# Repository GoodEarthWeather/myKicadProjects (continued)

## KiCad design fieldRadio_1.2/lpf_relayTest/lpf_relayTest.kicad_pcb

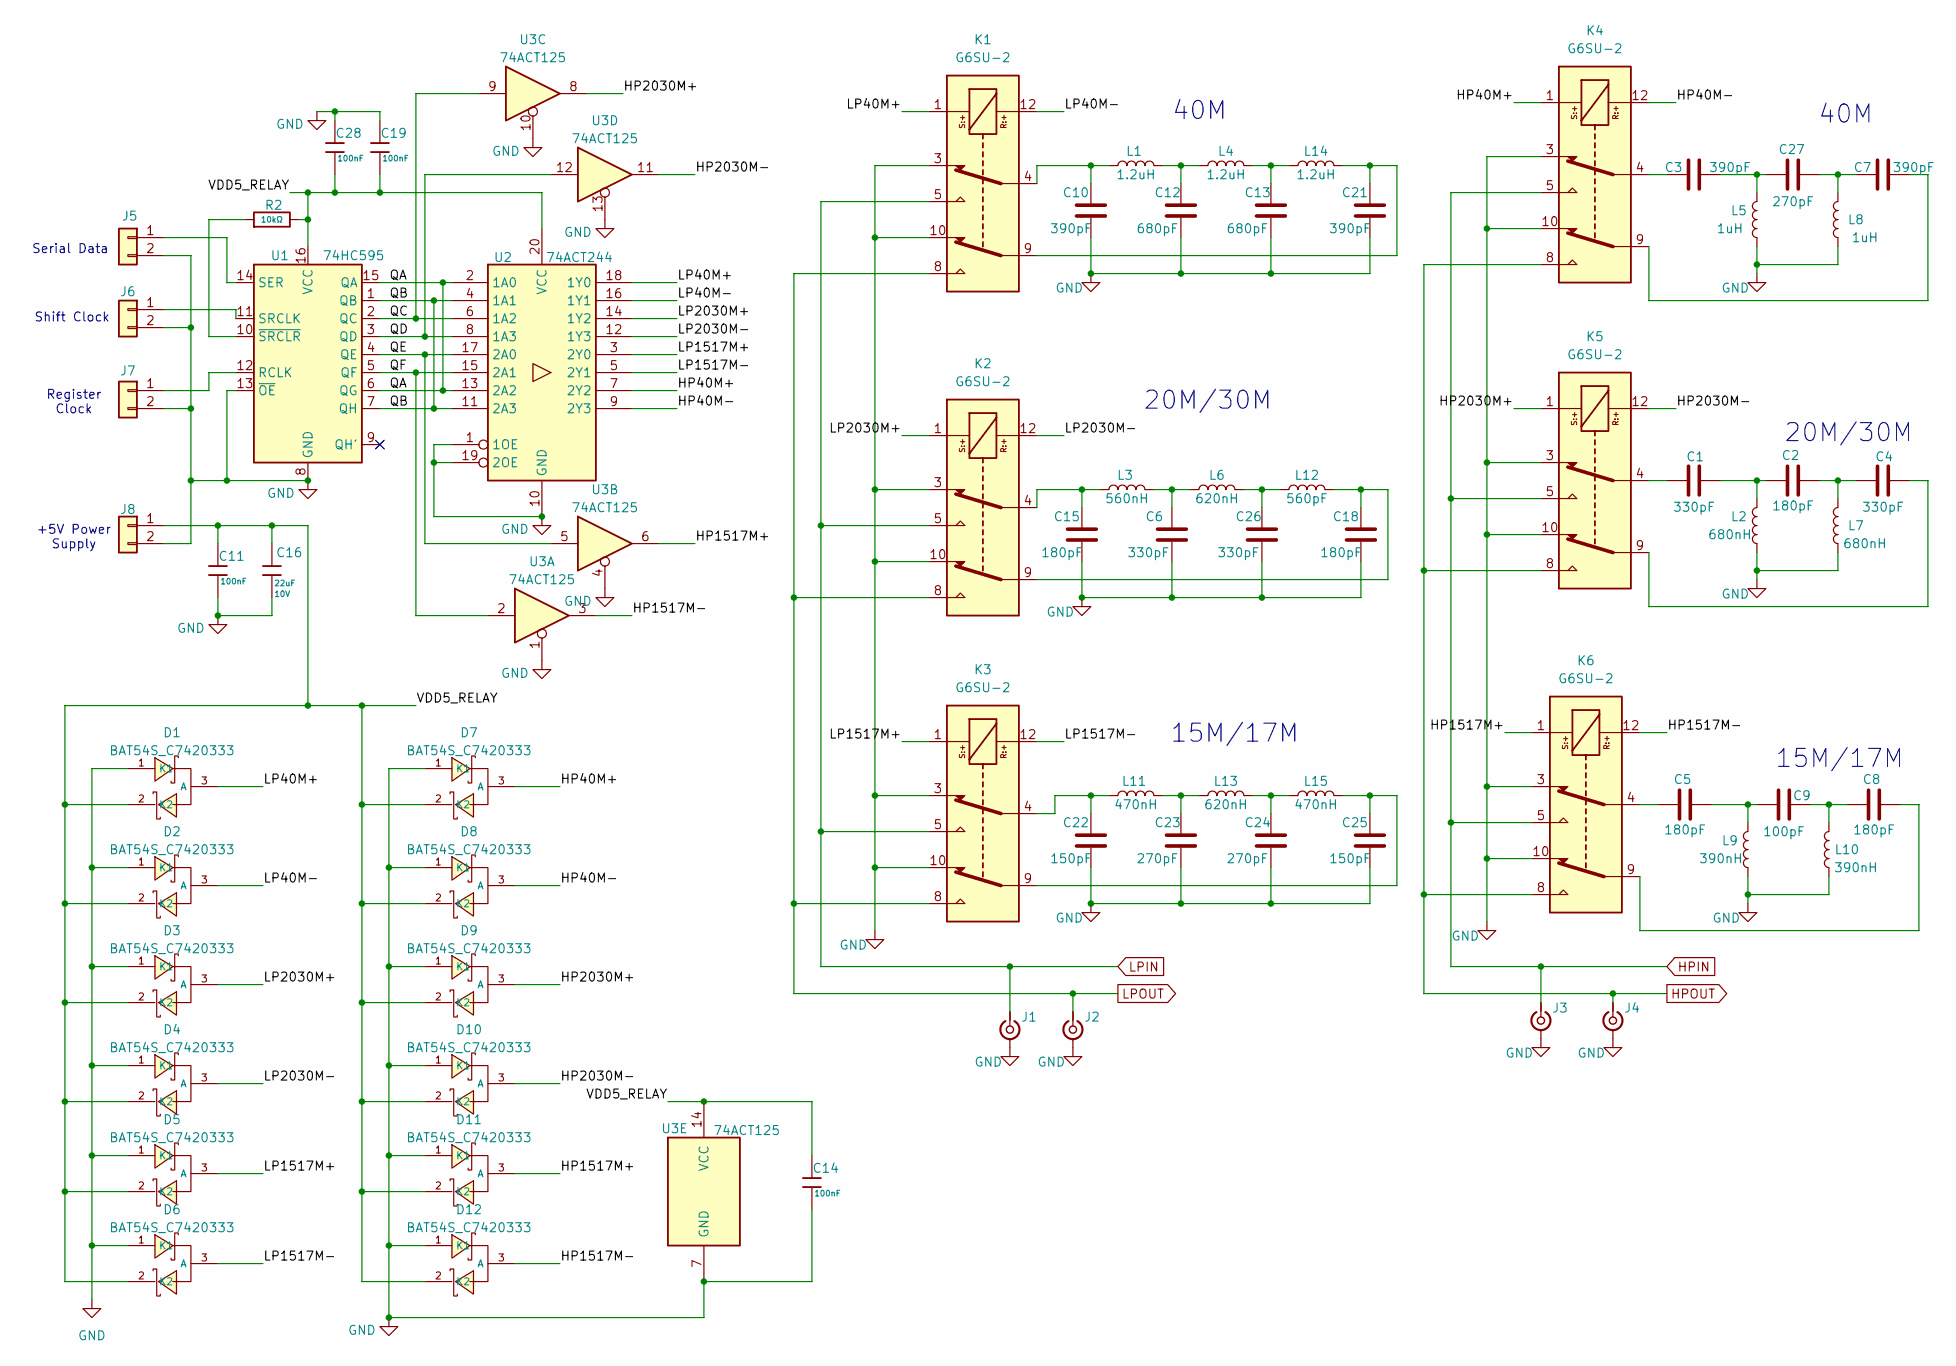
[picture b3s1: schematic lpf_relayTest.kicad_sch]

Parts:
C1, C4, C6, C26: 330pF; C_0805_2012Metric_Pad1.18x1.45mm_HandSolder; jlcpcb C113820
C2, C5, C8, C15, C18: 180pF; C_0805_2012Metric_Pad1.18x1.45mm_HandSolder; jlcpcb C527205
C3, C7, C10, C21: 390pF; C_0805_2012Metric_Pad1.18x1.45mm_HandSolder; jlcpcb C527206
C9: 100pF; C_0805_2012Metric_Pad1.18x1.45mm_HandSolder; jlcpcb C107105
C11, C14, C19, C28: 100nF; C_0603; Voltage Rated 50V; Tolerance ±10%; Part CC0603KRX7R9BB104; LCSC C14663
C12, C13: 680pF; C_0805_2012Metric_Pad1.18x1.45mm_HandSolder; jlcpcb C513601
C16: 22uF; C_1206; Voltage Rated 10V; Tolerance ±10%; Part CL31A226KPHNNNE; LCSC C5672
C22, C25: 150pF; C_0805_2012Metric_Pad1.18x1.45mm_HandSolder; jlcpcb C576916
C23, C24, C27: 270pF; C_0805_2012Metric_Pad1.18x1.45mm_HandSolder; jlcpcb C107106
D1, D2, D3, D4, D5, D6, D7, D8, D9, D10, D11, D12: BAT54S_C7420333; SOT-23-3_L2.9-W1.3-P1.90-LS2.4-BR; Reverse Voltage (Vr) 30V; Forward Voltage (Vf@If) 0.4V@10mA; Part BAT54S; LCSC C7420333
J1, J2, J3, J4: Conn_Coaxial_Small; SMA_Samtec_SMA-J-P-H-ST-EM1_EdgeMount
J5, J6, J7, J8: Conn_01x02; PinHeader_1x02_P2.54mm_Vertical
K1, K2, K3, K4, K5, K6: G6SU-2; Relay_DPDT_Omron_G6S-2F; Mouser Part Number 653-G6SU-2F-TRDC5
L1, L4, L14: 1.2uH; L_Toroid_Vertical_L13.0mm_W6.5mm_P5.60mm
L2, L7: 680nH; L_Toroid_Vertical_L13.0mm_W6.5mm_P5.60mm
L3: 560nH; L_Toroid_Vertical_L13.0mm_W6.5mm_P5.60mm
L5, L8: 1uH; L_Toroid_Vertical_L13.0mm_W6.5mm_P5.60mm
L6, L13: 620nH; L_Toroid_Vertical_L13.0mm_W6.5mm_P5.60mm
L9, L10: 390nH; L_Toroid_Vertical_L13.0mm_W6.5mm_P5.60mm
L11, L15: 470nH; L_Toroid_Vertical_L13.0mm_W6.5mm_P5.60mm
L12: 560pF; L_Toroid_Vertical_L13.0mm_W6.5mm_P5.60mm
R2: 10kΩ; R_0603; Overload Voltage (Max) 75V; Tolerance ±1%; Part 0603WAF1002T5E; LCSC C25804
U1: 74HC595; SOIC-16_3.9x9.9mm_P1.27mm; jlcpcb C10092
U2: 74ACT244; TSSOP-20_4.4x6.5mm_P0.65mm; jlcpcb C6930
U3: 74ACT125; SOIC-14_3.9x8.7mm_P1.27mm; jlcpcb C113254

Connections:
/HP40M+: D7.3 (A), K4.1, U2.7 (2Y2)
/HP40M-: D8.3 (A), K4.12, U2.9 (2Y3)
/HP1517M+: D11.3 (A), K6.1, U3.6
/HP1517M-: D12.3 (A), K6.12, U3.3
/HP2030M+: D9.3 (A), K5.1, U3.8
/HP2030M-: D10.3 (A), K5.12, U3.11
/LP40M+: D1.3 (A), K1.1, U2.18 (1Y0)
/LP40M-: D2.3 (A), K1.12, U2.16 (1Y1)
/LP1517M+: D5.3 (A), K3.1, U2.3 (2Y0)
/LP1517M-: D6.3 (A), K3.12, U2.5 (2Y1)
/LP2030M+: D3.3 (A), K2.1, U2.14 (1Y2)
/LP2030M-: D4.3 (A), K2.12, U2.12 (1Y3)
/QA: U1.6 (QG), U1.15 (QA), U2.2 (1A0), U2.13 (2A2)
/QB: U1.1 (QB), U1.7 (QH), U2.4 (1A1), U2.11 (2A3)
/QC: U1.2 (QC), U2.6 (1A2), U3.9
/QD: U1.3 (QD), U2.8 (1A3), U3.12
/QE: U1.4 (QE), U2.17 (2A0), U3.5
/QF: U1.5 (QF), U2.15 (2A1), U3.2
/VDD5_RELAY: C11.1, C14.1, C16.1, C19.2, C28.2, D1.2 (K2), D2.2 (K2), D3.2 (K2), D4.2 (K2), D5.2 (K2), D6.2 (K2), D7.2 (K2), D8.2 (K2), D9.2 (K2), D10.2 (K2), D11.2 (K2), D12.2 (K2), J8.1, R2.2, U1.16 (VCC), U2.20 (VCC), U3.14 (VCC)
GND: C6.2, C10.2, C11.2, C12.2, C13.2, C14.2, C15.2, C16.2, C18.2, C19.1, C21.2, C22.2, C23.2, C24.2, C25.2, C26.2, C28.1, D1.1 (K1), D2.1 (K1), D3.1 (K1), D4.1 (K1), D5.1 (K1), D6.1 (K1), D7.1 (K1), D8.1 (K1), D9.1 (K1), D10.1 (K1), D11.1 (K1), D12.1 (K1), J1.2 (Ext), J2.2 (Ext), J3.2 (Ext), J4.2 (Ext), J5.2, J6.2, J7.2, J8.2, K1.3, K1.10, K2.3, K2.10, K3.3, K3.10, K4.3, K4.10, K5.3, K5.10, K6.3, K6.10, L2.2, L5.2, L7.2, L8.2, L9.2, L10.2, U1.8 (GND), U1.13 (~OE), U2.1 (1OE), U2.10 (GND), U2.19 (2OE), U3.1, U3.4, U3.7 (GND), U3.10, U3.13
HPIN: J3.1 (In), K4.5, K5.5, K6.5
HPOUT: J4.1 (In), K4.8, K5.8, K6.8
LPIN: J1.1 (In), K1.5, K2.5, K3.5
LPOUT: J2.1 (In), K1.8, K2.8, K3.8
unnamed: C1.1, K5.4
unnamed: C1.2, C2.1, L2.1
unnamed: C2.2, C4.1, L7.1
unnamed: C3.1, K4.4
unnamed: C4.2, K5.9
unnamed: C5.1, K6.4
unnamed: C5.2, C9.2, L9.1
unnamed: C6.1, L3.2, L6.1
unnamed: C7.2, K4.9
unnamed: C8.1, C9.1, L10.1
unnamed: C8.2, K6.9
unnamed: C10.1, K1.4, L1.1
unnamed: C12.1, L1.2, L4.1
unnamed: C13.1, L4.2, L14.1
unnamed: C15.1, K2.4, L3.1
unnamed: C18.1, K2.9, L12.2
unnamed: C21.1, K1.9, L14.2
unnamed: C22.1, K3.4, L11.1
unnamed: C23.1, L11.2, L13.1
unnamed: C24.1, L13.2, L15.1
unnamed: C25.1, K3.9, L15.2
unnamed: C26.1, L6.2, L12.1
unnamed: C3.2, C27.1, L5.1
unnamed: C7.1, C27.2, L8.1
unnamed: J5.1, U1.14 (SER)
unnamed: J6.1, U1.11 (SRCLK)
unnamed: J7.1, U1.12 (RCLK)
unnamed: R2.1, U1.10 (~SRCLR)

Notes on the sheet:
15M/17M
Serial Data
Register Clock
Shift Clock
20M/30M
40M
+5V Power Supply

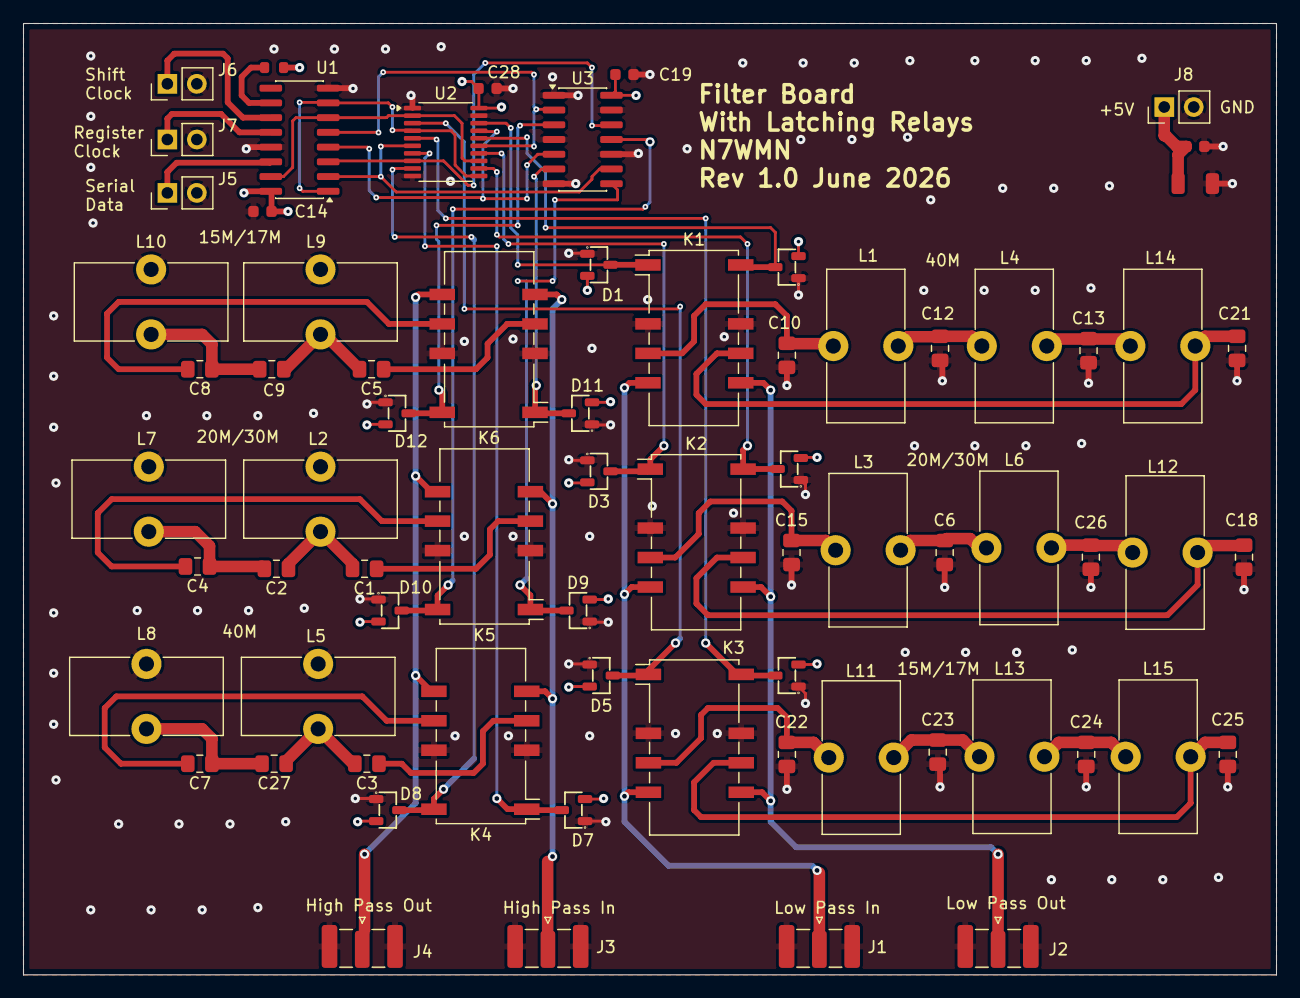
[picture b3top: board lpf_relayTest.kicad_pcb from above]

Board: 4 copper layers, 108.0 x 82.0 mm, 71 parts (0 on the bottom side), 52 nets.

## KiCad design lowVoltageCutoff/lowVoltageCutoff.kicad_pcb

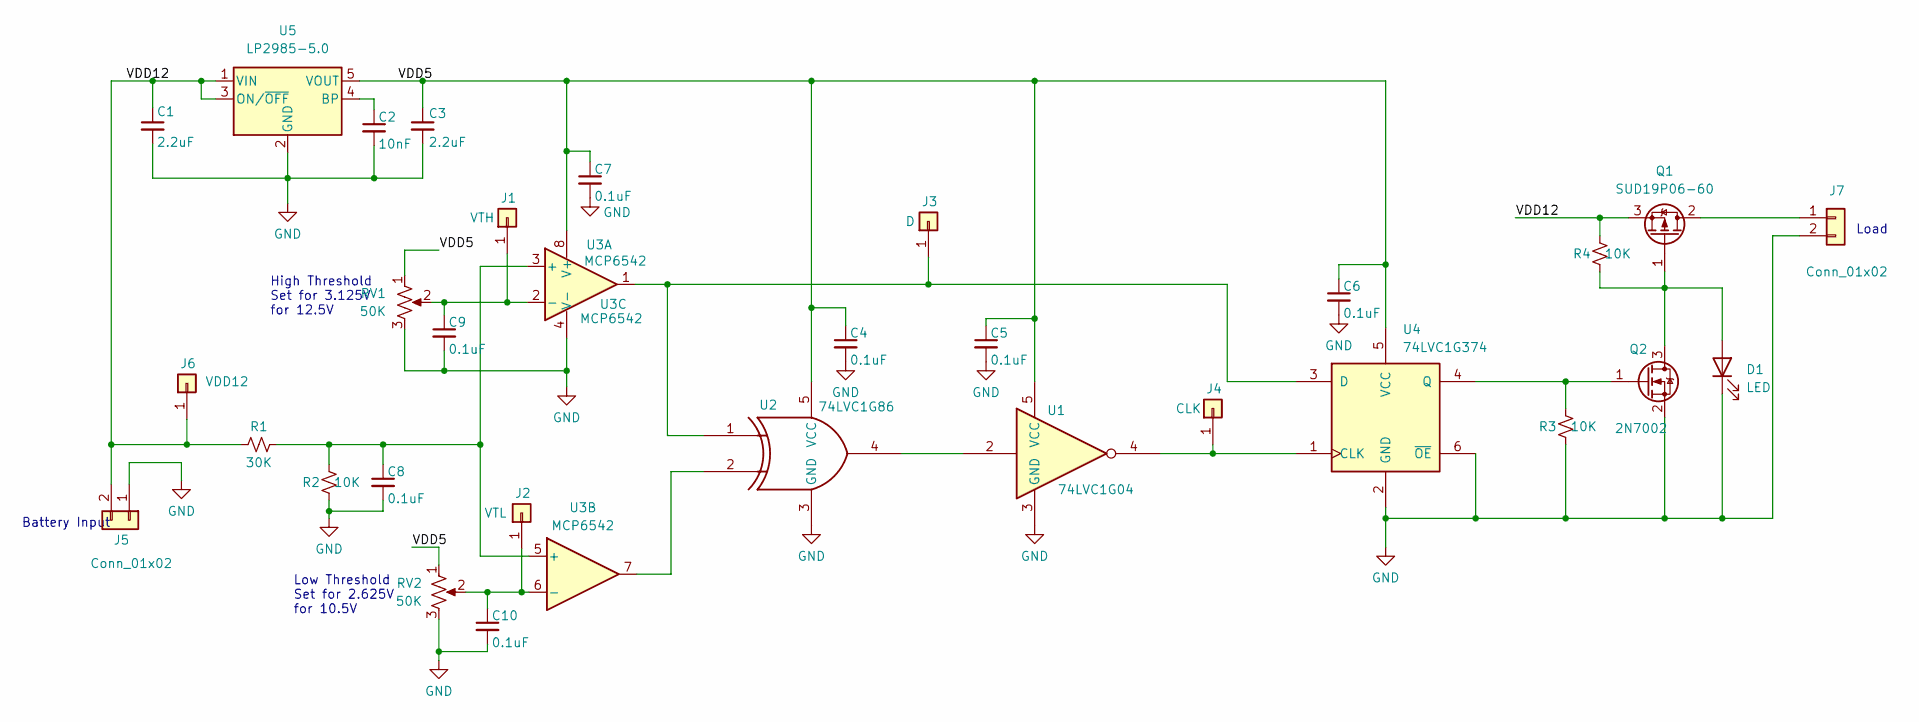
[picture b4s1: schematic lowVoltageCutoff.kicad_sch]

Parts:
C1, C3: 2.2uF; C_0603_1608Metric_Pad1.08x0.95mm_HandSolder
C2: 10nF; C_0603_1608Metric_Pad1.08x0.95mm_HandSolder
C4, C5, C6, C7, C8, C9, C10: 0.1uF; C_0603_1608Metric_Pad1.08x0.95mm_HandSolder
D1: LED; LED_D5.0mm
J1: VTH; PinHeader_1x01_P2.54mm_Vertical
J2: VTL; PinHeader_1x01_P2.54mm_Vertical
J3: D; PinHeader_1x01_P2.54mm_Vertical
J4: CLK; PinHeader_1x01_P2.54mm_Vertical
J5, J7: Conn_01x02; PinHeader_1x02_P2.54mm_Vertical
J6: VDD12; PinHeader_1x01_P2.54mm_Vertical
Q1: SUD19P06-60; TO-252-2; Mouser PN 781-SUD19P06-60L-E3
Q2: 2N7002; SOT-23
R1: 30K; R_0603_1608Metric_Pad0.98x0.95mm_HandSolder
R2, R3, R4: 10K; R_0603_1608Metric_Pad0.98x0.95mm_HandSolder
RV1, RV2: 50K; Potentiometer_Bourns_3296W_Vertical
U1: 74LVC1G04; SOT-23-5_HandSoldering; MouserPN 595-SN74LVC1G04DBVR
U2: 74LVC1G86; SOT-23-5_HandSoldering; Mouser PN 595-SN74LVC1G86DBVR
U3: MCP6542; SOIC-8_3.9x4.9mm_P1.27mm; Mouser PN 579-MCP6542T-I/SN
U4: 74LVC1G374; SOT-23-6_Handsoldering; Mouser PN 595-SN74LVC1G374DBVR
U5: LP2985-5.0; SOT-23-5_HandSoldering; Mouser PN 926-LP2985AIM5X50NPB

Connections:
/VDD5: C3.1, C4.1, C5.1, C6.1, C7.1, RV1.1, RV2.1, U1.5 (VCC), U2.5 (VCC), U3.8 (V+), U4.5 (VCC), U5.5 (VOUT)
/VDD12: C1.1, J5.2, J6.1, Q1.3 (S), R1.1, R4.2, U5.1 (VIN), U5.3 (ON/~OFF)
GND: C1.2, C2.2, C3.2, C4.2, C5.2, C6.2, C7.2, C8.2, C9.2, C10.2, D1.1 (K), J5.1, J7.2, Q2.2 (S), R2.1, R3.1, RV1.3, RV2.3, U1.3 (GND), U2.3 (GND), U3.4 (V-), U4.2 (GND), U4.6 (~OE), U5.2 (GND)
unnamed: D1.2 (A), Q1.1 (G), Q2.3 (D), R4.1
unnamed: C9.1, J1.1, RV1.2, U3.2 (-)
unnamed: C10.1, J2.1, RV2.2, U3.6 (-)
unnamed: J3.1, U2.1, U3.1, U4.3 (D)
unnamed: J4.1, U1.4, U4.1 (CLK)
unnamed: J7.1, Q1.2 (D)
unnamed: Q2.1 (G), R3.2, U4.4 (Q)
unnamed: U1.2, U2.4
unnamed: U2.2, U3.7
unnamed: C8.1, R1.2, R2.2, U3.3 (+), U3.5 (+)
unnamed: C2.1, U5.4 (BP)

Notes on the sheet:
Load
Battery Input
Low Threshold Set for 2.625V for 10.5V
High Threshold Set for 3.125V for 12.5V

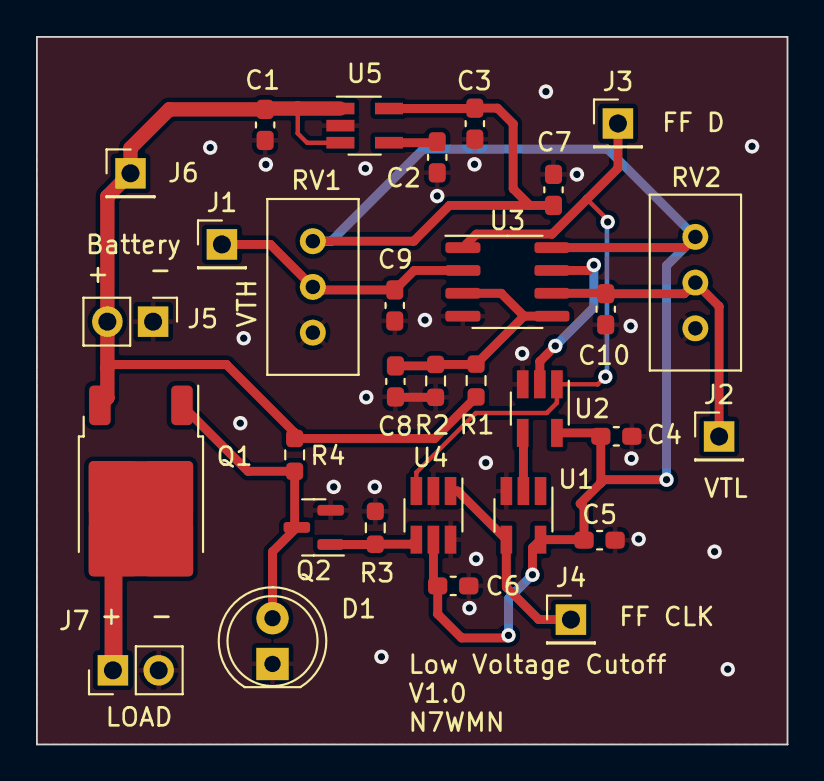
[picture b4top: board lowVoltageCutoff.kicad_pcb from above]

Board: 2 copper layers, 41.7 x 39.3 mm, 31 parts (0 on the bottom side), 14 nets.

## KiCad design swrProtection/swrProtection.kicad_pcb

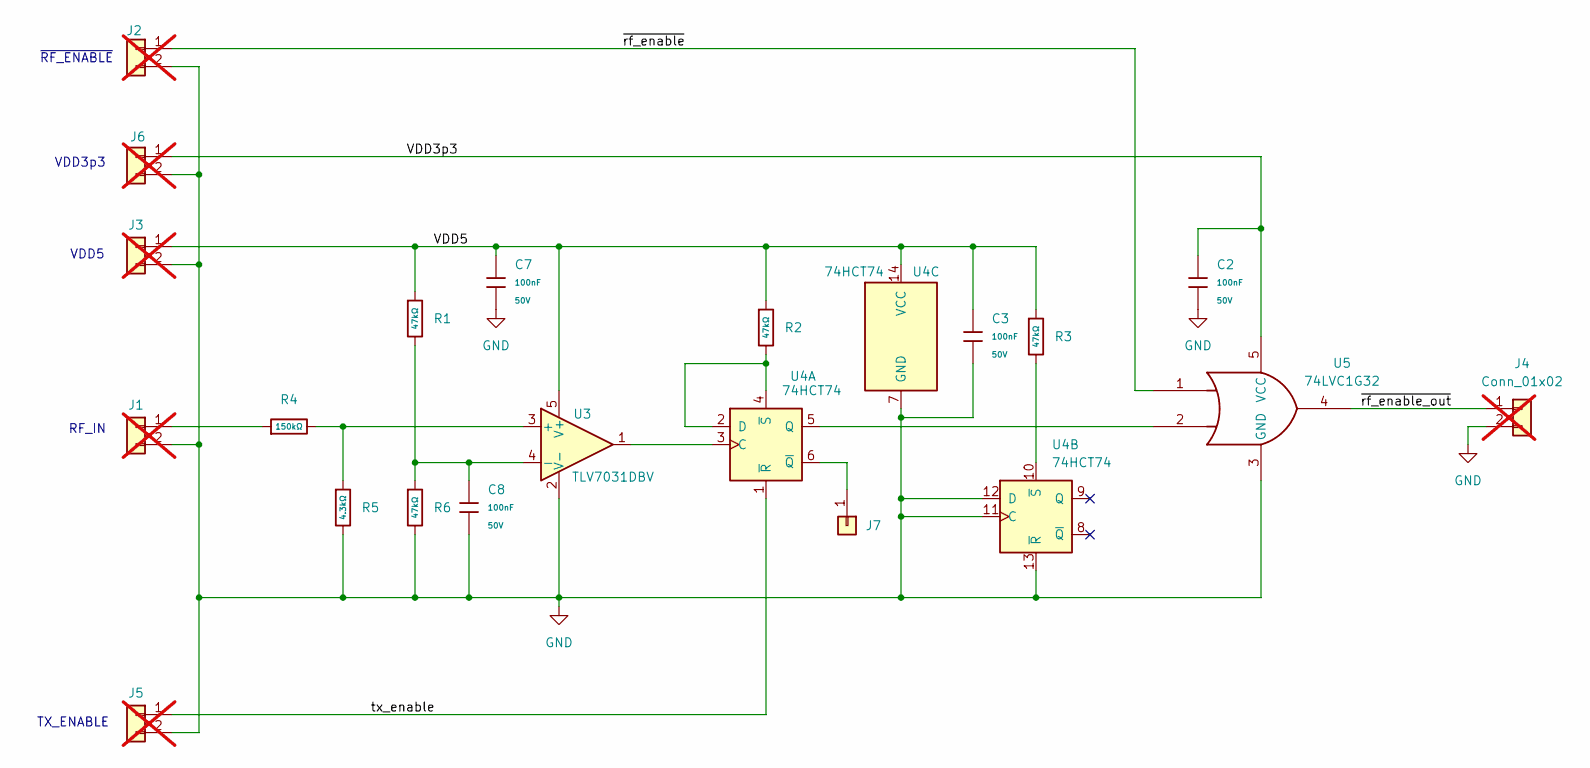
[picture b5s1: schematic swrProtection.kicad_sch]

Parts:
C2, C3, C7, C8: 100nF; C_0603; Voltage Rated 50V; Tolerance ±10%; Part CC0603KRX7R9BB104; LCSC C14663
J1, J2, J3, J4, J5, J6: Conn_01x02; PinHeader_1x02_P2.54mm_Vertical; not fitted
J7: Conn_01x01; PinHeader_1x01_P2.54mm_Vertical
R1, R2, R3, R6: 47kΩ; R_0603; Overload Voltage (Max) 75V; Tolerance ±1%; Part 0603WAF4702T5E; LCSC C25819
R4: 150kΩ; R_0603; Overload Voltage (Max) 75V; Tolerance ±1%; Part 0603WAF1503T5E; LCSC C22807
R5: 4.3kΩ; R_0603; Overload Voltage (Max) 75V; Tolerance ±1%; Part 0603WAF4301T5E; LCSC C23159
U3: TLV7031DBV; SOT-23-5; LCSC C2869832
U4: 74HCT74; SO-14_3.9x8.65mm_P1.27mm; LCSC C352961
U5: 74LVC1G32; SOT-23-5; LCSC C10096

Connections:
/VDD3p3: C2.1, J6.1, U5.5 (VCC)
/VDD5: C3.1, C7.1, J3.1, R1.1, R2.1, R3.1, U3.5 (V+), U4.14 (VCC)
/tx_enable: J5.1, U4.1 (~R)
/~rf_enable_out: J4.1, U5.4
/~rf_enable: J2.1, U5.1
GND: C2.2, C3.2, C7.2, C8.2, J1.2, J2.2, J3.2, J4.2, J5.2, J6.2, R5.2, R6.2, U3.2 (V-), U4.7 (GND), U4.11 (C), U4.12 (D), U4.13 (~R), U5.3 (GND)
unnamed: J1.1, R4.1
unnamed: J7.1, U4.6 (~Q)
unnamed: R4.2, R5.1, U3.3 (+)
unnamed: C8.1, R1.2, R6.1, U3.4 (-)
unnamed: U3.1, U4.3 (C)
unnamed: R2.2, U4.2 (D), U4.4 (~S)
unnamed: U4.5 (Q), U5.2
unnamed: R3.2, U4.10 (~S)

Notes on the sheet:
VDD5
VDD3p3
~{RF_ENABLE}
TX_ENABLE
RF_IN

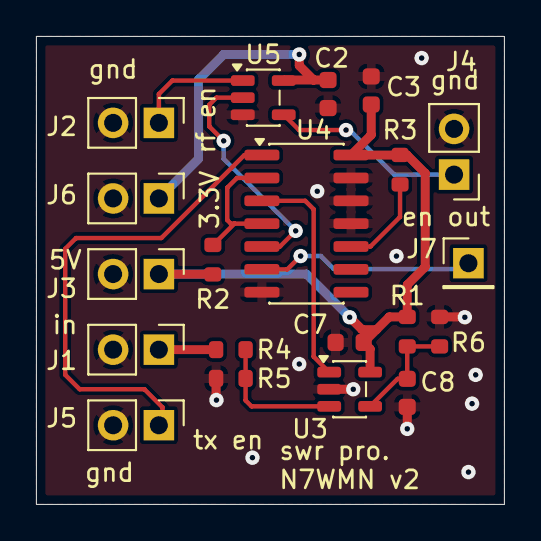
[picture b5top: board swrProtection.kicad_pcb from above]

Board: 2 copper layers, 26.0 x 26.0 mm, 20 parts (0 on the bottom side), 14 nets.
